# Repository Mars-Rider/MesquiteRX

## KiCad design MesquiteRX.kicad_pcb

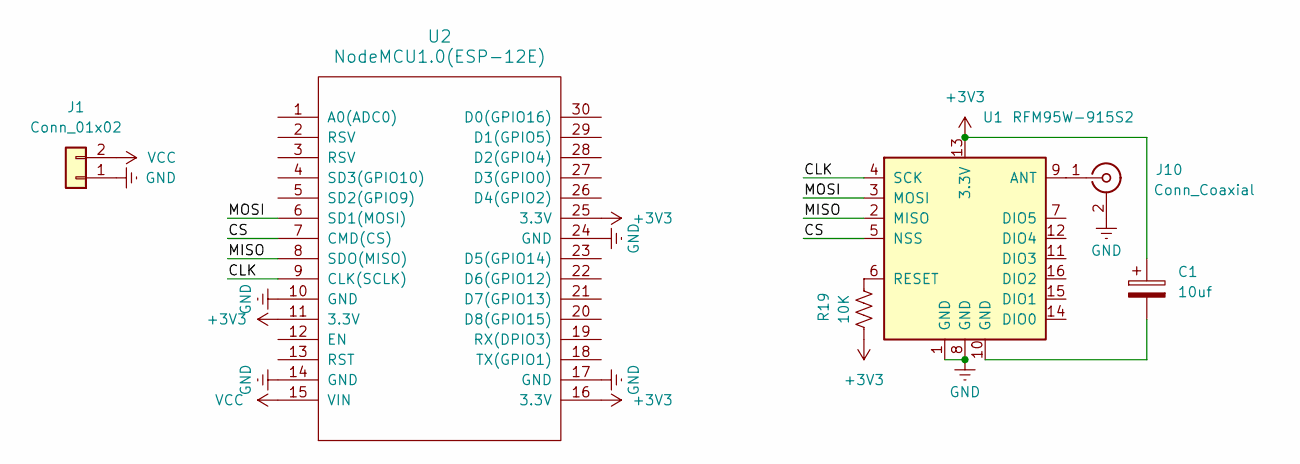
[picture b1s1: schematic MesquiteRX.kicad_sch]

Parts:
C1: 10uf; CP_Radial_D4.0mm_P1.50mm
J1: Conn_01x02; JST_PH_B2B-PH-K_1x02_P2.00mm_Vertical
J10: Conn_Coaxial; SMA_Amphenol_132289_EdgeMount; MPN 132289
R19: 10K; R_Axial_DIN0207_L6.3mm_D2.5mm_P10.16mm_Horizontal
U1: RFM95W-915S2; MODULE_RFM96W-433S2
U2: NodeMCU1.0(ESP-12E); ESP12F-Devkit-V3

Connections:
+3V3: C1.1, R19.1, U1.13 (3.3V), U2.11 (3.3V), U2.16 (3.3V), U2.25 (3.3V)
/CLK: U1.4 (SCK), U2.9 (CLK(SCLK))
/CS: U1.5 (NSS), U2.7 (CMD(CS))
/MISO: U1.2 (MISO), U2.8 (SDO(MISO))
/MOSI: U1.3 (MOSI), U2.6 (SD1(MOSI))
GND: J1.1, J10.2 (Ext), U1.1 (GND), U1.8 (GND), U2.10 (GND), U2.14 (GND), U2.17 (GND), U2.24 (GND)
unnamed: C1.2, U1.10 (GND)
unnamed: J10.1 (In), U1.9 (ANT)
unnamed: R19.2, U1.6 (RESET)
VCC: J1.2, U2.15 (VIN)

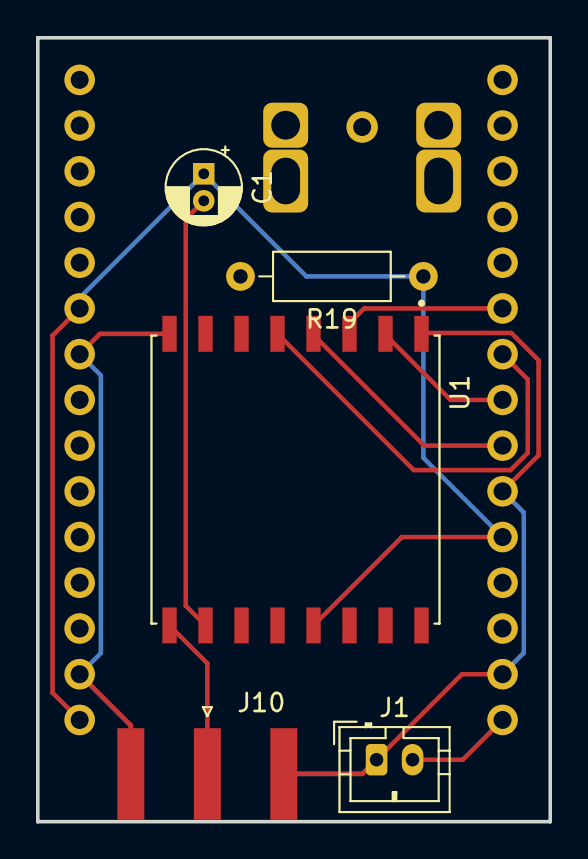
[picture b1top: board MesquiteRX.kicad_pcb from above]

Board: 2 copper layers, 28.5 x 43.5 mm, 6 parts (1 on the bottom side), 10 nets.
